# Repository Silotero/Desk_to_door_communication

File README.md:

# Desk_to_door_communication

This is a 2-part project. Its purpose is to establish basic communication beetween a person that is sitting inside the room at his desk and a visitor standing outside his rooms door. It allows the person in the room to display certain information (such as what he is doing, is he busy, can the person outside easily enter) at a screen outside near the doors, for the visitor. The visitor can also send certain information such as announcing who he is, to the person at the desk. Also displayed at a small screen.
Other functions are a webhosted camera view of the outside of the room, a RFID tag reader that displays certain information on the screen after a readout and also plays a song on the speakers.

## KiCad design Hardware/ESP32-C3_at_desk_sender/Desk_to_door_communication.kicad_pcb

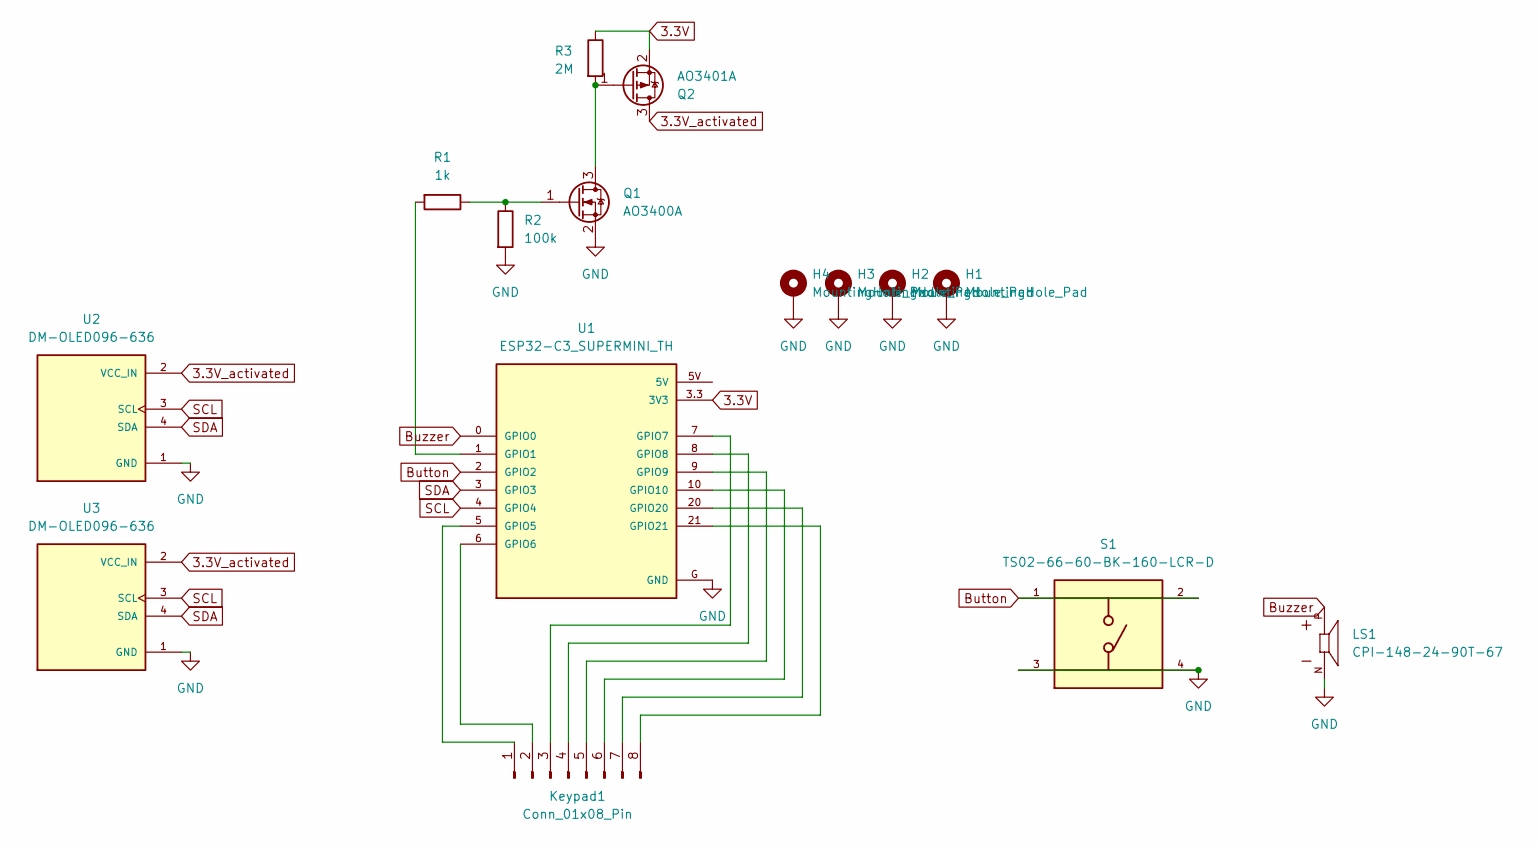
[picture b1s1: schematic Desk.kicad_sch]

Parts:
H1, H2, H3, H4: MountingHole_Pad; MountingHole_2.2mm_M2_DIN965_Pad_TopBottom
Keypad1: Conn_01x08_Pin; PinHeader_1x08_P2.54mm_Vertical
LS1: CPI-148-24-90T-67; XDCR_CPI-148-24-90T-67; PARTREV 1
Q1: AO3400A; SOT-23
Q2: AO3401A; SOT-23
R1: 1k; R_0805_2012Metric
R2: 100k; R_0805_2012Metric
R3: 2M; R_0805_2012Metric
S1: TS02-66-60-BK-160-LCR-D; SW_TS02-66-60-BK-160-LCR-D; PARTREV 1.0
U1: ESP32-C3_SUPERMINI_TH; MODULE_ESP32-C3_SUPERMINI_TH
U2, U3: DM-OLED096-636; MODULE_DM-OLED096-636; PARTREV 2018-09-10

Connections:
3.3V: Q2.2 (S), R3.1, U1.3.3 (3V3)
3.3V_activated: Q2.3 (D), U2.2 (VCC_IN), U3.2 (VCC_IN)
Button: S1.1, S1.2, U1.2 (GPIO2)
Buzzer: LS1.P, U1.0 (GPIO0)
GND: H1.1, H2.1, H3.1, H4.1, LS1.N, Q1.2 (S), R2.2, S1.3, S1.4, U1.G (GND), U2.1 (GND), U3.1 (GND)
unnamed: Keypad1.1, U1.5 (GPIO5)
unnamed: Keypad1.2, U1.6 (GPIO6)
unnamed: Keypad1.3, U1.7 (GPIO7)
unnamed: Keypad1.4, U1.8 (GPIO8)
unnamed: Keypad1.5, U1.9 (GPIO9)
unnamed: Keypad1.6, U1.10 (GPIO10)
unnamed: Keypad1.7, U1.20 (GPIO20)
unnamed: Keypad1.8, U1.21 (GPIO21)
unnamed: Q1.3 (D), Q2.1 (G), R3.2
unnamed: Q1.1 (G), R1.1, R2.1
unnamed: R1.2, U1.1 (GPIO1)
SCL: U1.4 (GPIO4), U2.3 (SCL), U3.3 (SCL)
SDA: U1.3 (GPIO3), U2.4 (SDA), U3.4 (SDA)

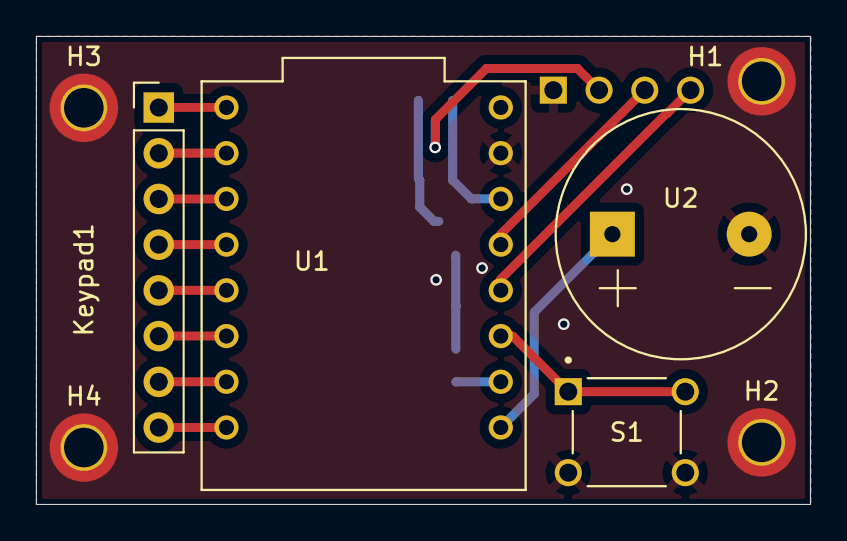
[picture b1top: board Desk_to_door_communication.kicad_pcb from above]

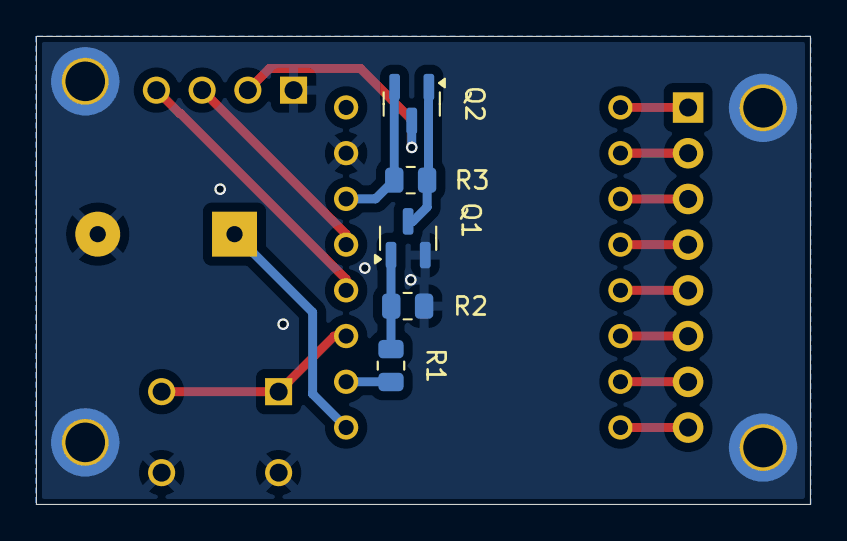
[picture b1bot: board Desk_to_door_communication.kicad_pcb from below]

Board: 2 copper layers, 43.0 x 26.0 mm, 14 parts (5 on the bottom side), 18 nets.

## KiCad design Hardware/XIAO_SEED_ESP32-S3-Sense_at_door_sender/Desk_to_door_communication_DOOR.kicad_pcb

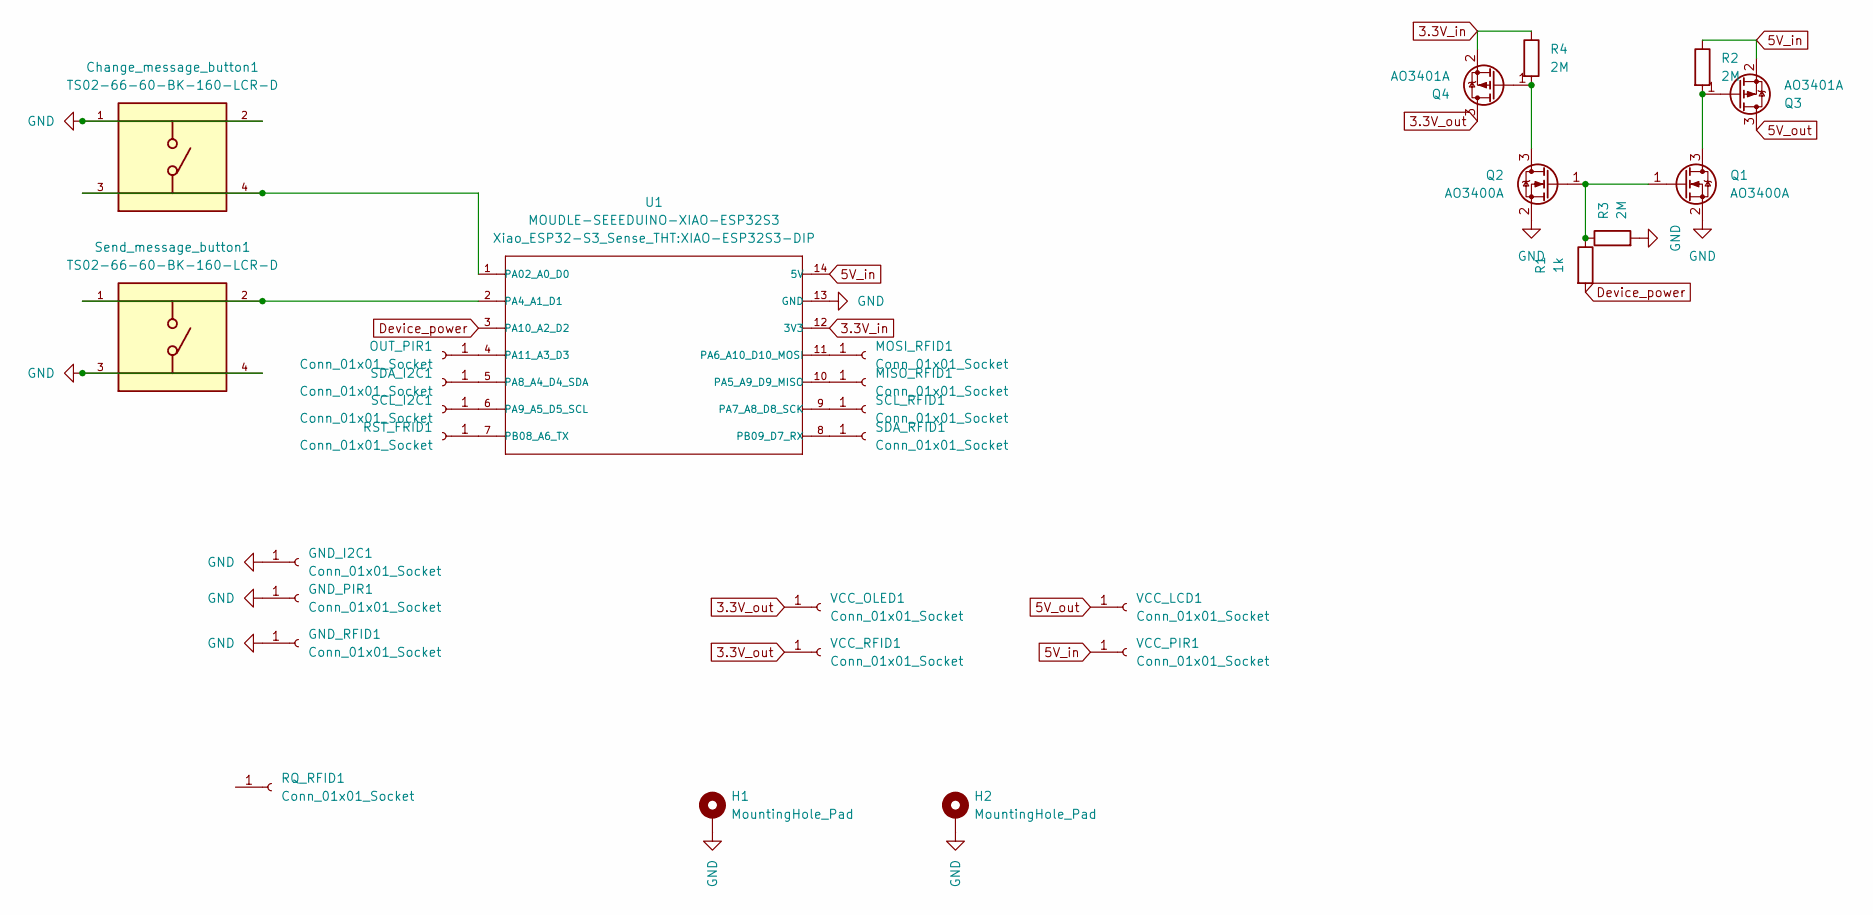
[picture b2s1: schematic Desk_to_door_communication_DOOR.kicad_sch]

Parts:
Change_message_button1: TS02-66-60-BK-160-LCR-D; SW_TS02-66-60-BK-160-LCR-D; PARTREV 1.0
GND_I2C1: Conn_01x01_Socket; Pin_D1.0mm_L10.0mm
GND_PIR1: Conn_01x01_Socket; Pin_D1.0mm_L10.0mm
GND_RFID1: Conn_01x01_Socket; Pin_D1.0mm_L10.0mm
H1, H2: MountingHole_Pad; MountingHole_2.2mm_M2_DIN965_Pad
MISO_RFID1: Conn_01x01_Socket; Pin_D1.0mm_L10.0mm
MOSI_RFID1: Conn_01x01_Socket; Pin_D1.0mm_L10.0mm
OUT_PIR1: Conn_01x01_Socket; Pin_D1.0mm_L10.0mm
Q1, Q2: AO3400A; SOT-23
Q3, Q4: AO3401A; SOT-23
R1: 1k; R_0805_2012Metric
R2, R3, R4: 2M; R_0805_2012Metric
RQ_RFID1: Conn_01x01_Socket; Pin_D1.0mm_L10.0mm
RST_FRID1: Conn_01x01_Socket; Pin_D1.0mm_L10.0mm
SCL_I2C1: Conn_01x01_Socket; Pin_D1.0mm_L10.0mm
SCL_RFID1: Conn_01x01_Socket; Pin_D1.0mm_L10.0mm
SDA_I2C1: Conn_01x01_Socket; Pin_D1.0mm_L10.0mm
SDA_RFID1: Conn_01x01_Socket; Pin_D1.0mm_L10.0mm
Send_message_button1: TS02-66-60-BK-160-LCR-D; SW_TS02-66-60-BK-160-LCR-D; PARTREV 1.0
U1: MOUDLE-SEEEDUINO-XIAO-ESP32S3; XIAO-ESP32S3-DIP
VCC_LCD1: Conn_01x01_Socket; Pin_D1.0mm_L10.0mm
VCC_OLED1: Conn_01x01_Socket; Pin_D1.0mm_L10.0mm
VCC_PIR1: Conn_01x01_Socket; Pin_D1.0mm_L10.0mm
VCC_RFID1: Conn_01x01_Socket; Pin_D1.0mm_L10.0mm

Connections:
3.3V_in: Q4.2 (S), R4.1, U1.12 (3V3)
3.3V_out: Q4.3 (D), VCC_OLED1.1, VCC_RFID1.1
5V_in: Q3.2 (S), R2.1, U1.14 (5V), VCC_PIR1.1
5V_out: Q3.3 (D), VCC_LCD1.1
Device_power: R1.2, U1.3 (PA10_A2_D2)
GND: Change_message_button1.1, Change_message_button1.2, GND_I2C1.1, GND_PIR1.1, GND_RFID1.1, H1.1, H2.1, Q1.2 (S), Q2.2 (S), R3.2, Send_message_button1.3, Send_message_button1.4, U1.13 (GND)
unnamed: MISO_RFID1.1, U1.10 (PA5_A9_D9_MISO)
unnamed: MOSI_RFID1.1, U1.11 (PA6_A10_D10_MOSI)
unnamed: OUT_PIR1.1, U1.4 (PA11_A3_D3)
unnamed: Q1.3 (D), Q3.1 (G), R2.2
unnamed: Q1.1 (G), Q2.1 (G), R1.1, R3.1
unnamed: Q2.3 (D), Q4.1 (G), R4.2
unnamed: RST_FRID1.1, U1.7 (PB08_A6_TX)
unnamed: SCL_I2C1.1, U1.6 (PA9_A5_D5_SCL)
unnamed: SCL_RFID1.1, U1.9 (PA7_A8_D8_SCK)
unnamed: SDA_I2C1.1, U1.5 (PA8_A4_D4_SDA)
unnamed: SDA_RFID1.1, U1.8 (PB09_D7_RX)
unnamed: Change_message_button1.3, Change_message_button1.4, U1.1 (PA02_A0_D0)
unnamed: Send_message_button1.1, Send_message_button1.2, U1.2 (PA4_A1_D1)

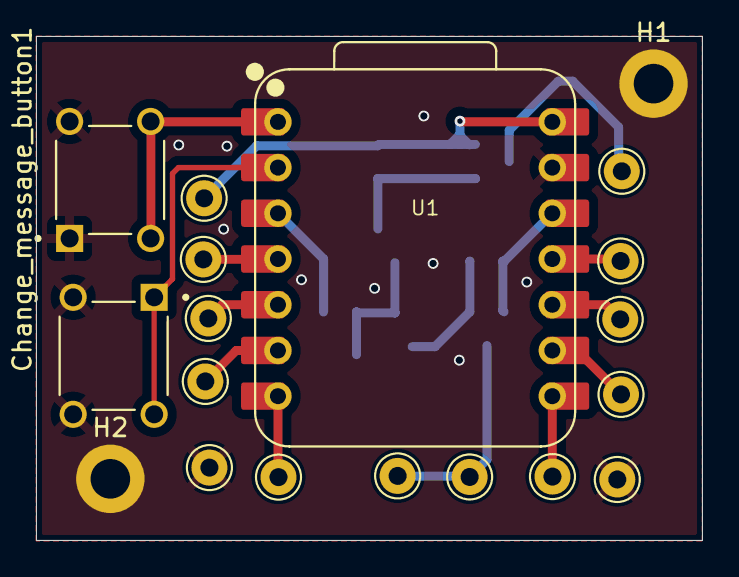
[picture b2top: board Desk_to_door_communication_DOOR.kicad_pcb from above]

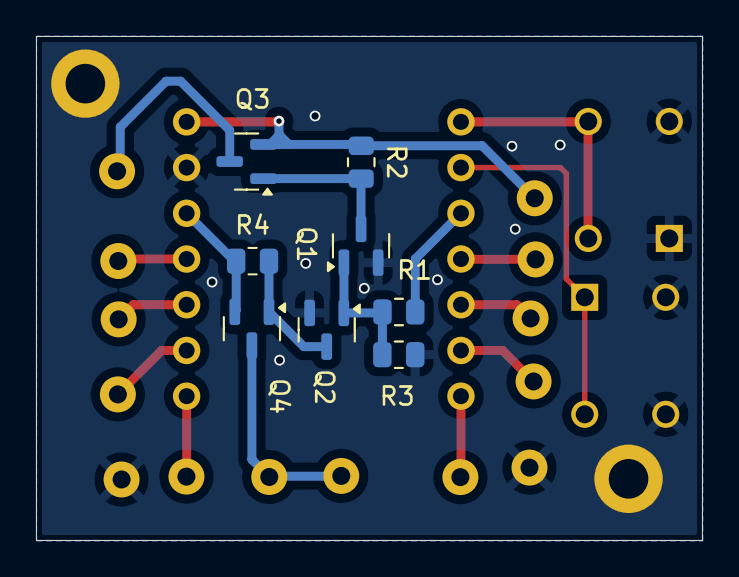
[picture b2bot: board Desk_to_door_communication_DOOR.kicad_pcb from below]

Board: 2 copper layers, 37.0 x 28.0 mm, 27 parts (8 on the bottom side), 19 nets.

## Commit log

2026-04-07 Added finished firmware
2026-04-07 Added finished hardware kicad files
